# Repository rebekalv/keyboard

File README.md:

# 🚀 Build Your Dream Mechanical LED Keyboard with AVR DU! 🌟

Ever wanted to craft your own custom mechanical keyboard? Here's how I brought mine to life, step-by-step! 🛠️✨

---

### 🔧 **Project Highlights:**

- **Microcontroller Magic 🧠:**  
  Powered by the AVR64DU32 on a Curiosity Nano (cnano), this keyboard communicates seamlessly via USB-C using the Human Interface Device (HID) class. No soldering, no hassle—just plug and play!

- **Custom PCB in KiCad 💻:**  
  I designed a PCB to eliminate complex wiring, ensuring a sleek, professional layout. KiCad made it easy to customize my PCB, but managing library includes can be somewhat cumbersome.

- **Light Up the Keys! 🌈:**  
  Each key features a NeoPixel-compatible LED beneath, adding customizable lighting effects. LEDs are programmed directly alongside the keyboard firmware using MPLAB X IDE. Imagine the rainbow possibilities! 🌟 Due to a pcb schematic error (red circles), the ground and led data pin were swapped. Which is why lighting the leds will have to wait untill the arrival of a new pcb.

- **Custom 3D-Printed Case 🎨:**  
  The case is here! Designed with simplicity and style, it’s split into five parts for easy 3D printing 🖨️. All .stl files are in the 3D_keyboard_case folder, ready to print and assemble.

---

🎹 **DIY Tip:** If you're diving into mechanical keyboard projects, understanding matrix scanning and pcb tools like KiCad will open up endless customization!

Ready to create your own masterpiece? Let's type into the future! 🚀

## Component List
- Microcontroller: [AVR64DU32 curiosity nano](https://www.microchip.com/en-us/development-tool/ev59f82a)
- LEDs: [3.2x2.8mm sk6812 mini-E, reverse mount neopixel LEDs](https://www.aliexpress.com/item/1005005193716172.html)
- Diodes: [1N4148 DO-35 through hole diodes](https://www.aliexpress.com/item/1005006127068810.html)
- Switches: [JWICK V2 T1 Black Blue Tactile Switch 5pin RGB, Cherry MX](https://www.aliexpress.com/item/1005004226805283.html)
- Stabilizers for big switches: [PCB mounted Cherry MX stabilizers](https://es.aliexpress.com/item/1005004229140548.html)
- See-through Keycaps: [Polychroma V2 RGB Keycaps, Nordic ISO](https://www.maxgaming.no/no/keycaps/polychroma-v2-rgb-keycaps-131-pbt-polykarbonat-caps-nordic-iso)

## Milestones
1. 🖥️ [**Layout Creation:**](#layout-creation) Sketch the perfect keyboard design.
2. 🛠️ [**AVR Pin Setup:**](#avr-pin-setup) Map out pin connections and wiring.
3. 🔌 [**Component Selection:**](#component-selection) Choose the ideal switches, diodes, and LEDs.
4. 📐 [**PCB Design:**](#pcb-design) Craft your circuit board in KiCad and send it for manufacturing.
5. 🔧 [**Assembly:**](#assembly) Solder components onto the PCB.
6. 💻 [**Firmware Development:**](#firmware-development) Program the AVR for matrix scanning.
7. 🌈 **LED Integration:** Synchronize lighting with the firmware. (Suspended untill new pcb)
8. 🏗️ [**Case Design:**](#case-design) Plan and 3D print your custom keyboard case
9. 📚 **Document Everything:** Share your journey and insights.

### Layout Creation
I used https://www.keyboard-layout-editor.com/ to create an initial layout for my keyboard. If you want to regenerate this design, go to the website and insert the raw json data from `keyboard_layout/raw_data.json`. 

When your design is ready, you will need the outline of the keyboard for the pcb design. Go to https://plate.keeb.io/ and paste the raw json data. Then you can then download the outline as an svg file.

### AVR Pin Setup
The important thing in this step is to map out how many pins your keyboard needs, and if your microcontroller can provide that. My keyboard needs 5 rows and 15 columns, hence 20 pins. Looking at pinout on the [cnano website](https://www.microchip.com/en-us/development-tool/ev59f82a), it has 24 port pins. Excluding the usb detect, LED control and debugger LED pin, we are left with 21 available pins, which is enough for our keyboard.

Reading the datasheet for the avrdu, it reveals that the usart0 signal can be routed to 4 possible transmission pins. We will use this signal to control the leds, and I chose alternative 3, PD4, as the LED_DATA pin.

### Component Selection
Check the [component list](#component-list) for handy links! Going with popular, widely-used components simplifies the PCB design, because pre-existing footprints save time and effort. That's why I selected the reliable Cherry MX switches alongside the 1N4148 DO-35 diodes. Some Cherry MX switches feature an opening for LEDs to shine through, perfect for illuminating your keyboard (see the marking on the picture below). I opted to solder everything manually, so I chose through-hole diodes and ensured the LEDs were hand-solderable.

Pro tip: Also, go for PCB-mounted stabilizers—they're far easier to install than plate mounted, and the PCB outline already accommodates them.

### PCB Design
Now the real fun begins! 🚀 Or maybe the challenge? 🛠️

#### Schematic
In KiCad, you’ll start by creating a clear and accurate schematic. This is the blueprint for your circuit, mapping out connections between components and ensuring everything fits together logically. Double-check those connections and that the schema matches the data sheets—it’s much easier to catch errors here than on a finished PCB!

In my schematics, I connected all my switches and diodes and assigned them rows and columns as described in the keyboard outline. Further, I designed a symbol for the avrdu cnano, with the pinout corresponding to the datasheet. I connected the rows and columns to available port pins, and the grounds, voltages and led pin to their corresponding pins.

#### PCB and 3D model
After completing the schematic, the next step is designing the PCB layout. In the pcb editor you can import the outline from `keyboard_layout/keyboard-outline.svg`, which lets you know where to place your components. 

Then you import all the components from the schematic and arrange the them according to your design outline. All the symbols from the schematics will be translated into their corresponding footprint, which can be a bit confunsing and I recommend watching a youtube video explaing in detail.

Now you need to route all the traces, which might be the most time consuming. The netlist, which is thin lines between your components, will show how everything should be connected.

You can double check that your design matches your vision by using the 3D viewer in kicad and assigning .step files to all your footprints. Here is the 3d model of the front and the back of my pcb:

Now your design is ready for production! I used the fabrication tool kit in KiCad, to create a .zip file with gerber files. Then I went to https://jlcpcb.com/, uploaded the file and sent it to production. 

Pro tip: If there are no footprints available for your microcontroller, you can use footprints for similar microcontrollers and manually add or remove holes in the footprint editor to match you preffered controller.

### Assembly
This is a very straight forward process where you solder your components on the pcb. Start with the diodes and leds and do the switches last. Here is the assembled keyboard with stabilizers:

### Firmware Development
The `full_keyboard_avrdu.X` project structure:
 - **usb**: For checking and maintaining the usb-c connection
 - **hardware**: Functions for scanning columns and activating rows
 - **main**: Handles keypresses and sends HID codes over usb
 - **keyboard**: Mapping of keypresses to HID codes
 - **led**: In progress, here you find general LED functions which I used in my summer project

#### Matrix Scanning
When a button is pressed, its column and its row are connected together. Since the active row is low, it will pull the column down, from high to low. The code sequentially activates each row and scans through all columns to detect keypresses. It detects both the change from high to low (key down) and from low to high (key up). This process is repeated continuously to monitor key presses.

```
void IterateColumns(void) // called every 1 ms
{  
    // Iterate columns
        // Check key down event
        // Check key up event
    }
    
    // Go to the next row
 
    return;
}
```

On each key change, press or release, a hid code is sent with either a press down or a press up event. 

```
void KeyPressHandler(uint8_t currentRow)
{
    DetectKeyChanges(currentRow);
    
    if (keyChanges)
    {
        if (keyDown)
        {
            KeyDownEvent();
        }
        else
        {
            KeyUpEvent();
        }
    }
}
```

For special characters, modifiers can be used (shift and ctrl). In my code I check if a keypress corresponds to a modifier and then send the modifier down or up event. 

### LED Integration
I used the usart0 in the AVR in spi mode, to create a pulse-width modulated signal for neopixel LEDs. This will be used later to control the color scheme of the LEDs, but is for now on hold.

### Case Design
The keyboard now has a home! I designed an awesome 3D keyboard case that’s both practical and fun 🎉. It’s split into five pieces to fit my 3D printer 🖨️ and is super easy to assemble. All the 3D modules are available in the 3D_keyboard_case folder as .stl files, ready to print in any color you want! 🛠️ For the creative minds, I’ve included the original DesignSpark Mechanical file 🖌️, so you can tweak, customize, or modify it using their 3D modeling software. Whether you glue it together, enhance it further, or leave it as is, this case is ready to elevate your keyboard project! 🚀🌈

  - Keyboard case top

- Keyboard case bottom

- Keyboard case tilted support

### Conclusion
Now you know how to create a custom, matrix keyboard using an AVR64DU32 Curiosity Nano. By using the USB-C HID class, our keyboard communicates directly with the computer and wiring was simplified using a custom made PCB. LEDs were included under each key and what is missing is to create a fitting case for the keyboard.

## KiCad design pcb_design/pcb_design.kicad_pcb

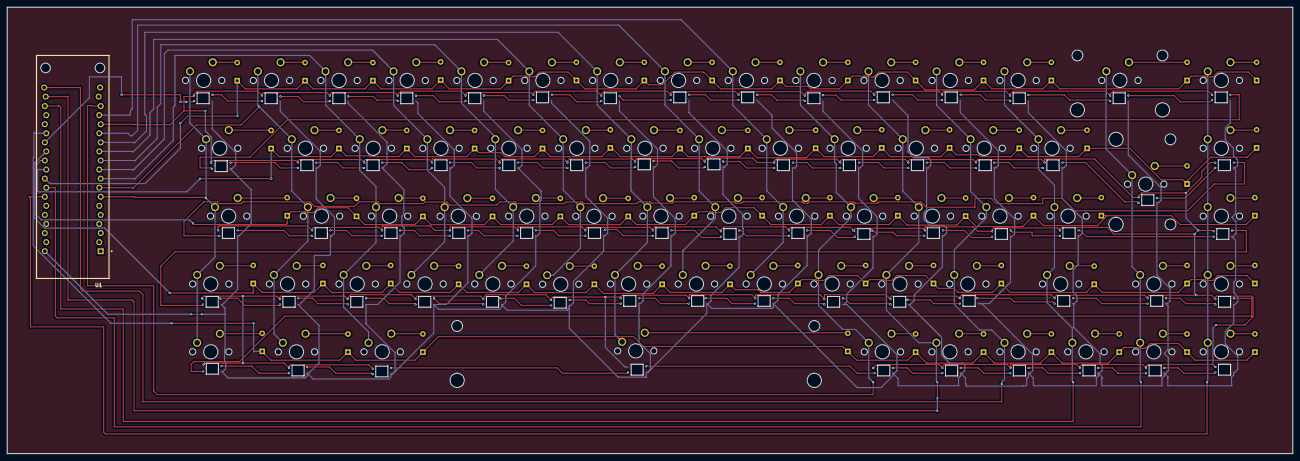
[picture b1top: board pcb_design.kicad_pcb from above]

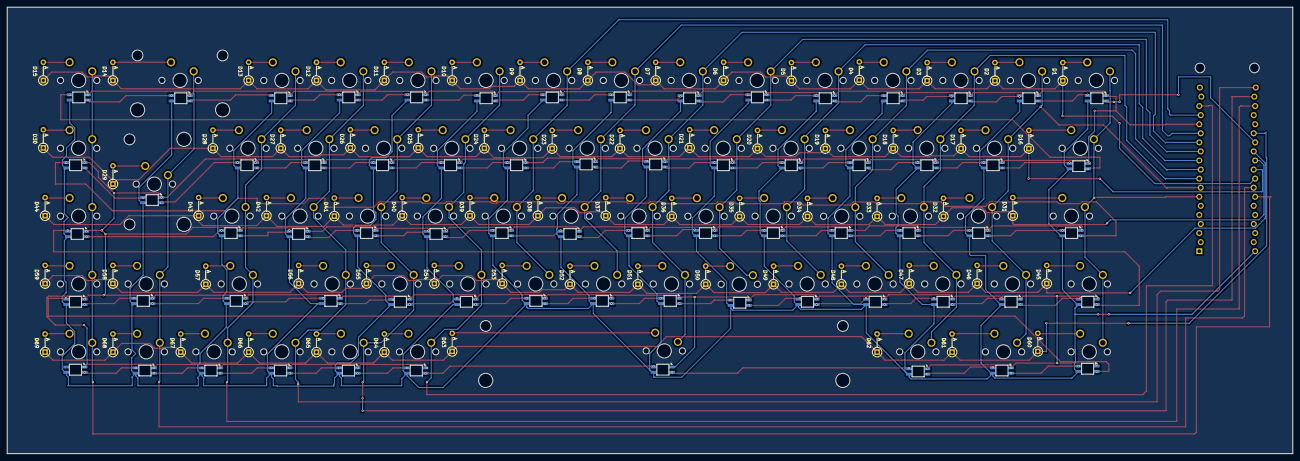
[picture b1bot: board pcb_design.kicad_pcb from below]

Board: 2 copper layers, 360.0 x 125.0 mm, 211 parts (138 on the bottom side), 160 nets.

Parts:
D1, D2, D3, D4, D5, D6, D7, D8, D9, D10, D11, D12, D13, D14, D15, D16, D17, D18, D19, D20, D21, D22, D23, D24, D25, D26, D27, D28, D29, D30, D31, D32, D33, D34, D35, D36, D37, D38, D39, D40, D41, D42, D43, D44, D45, D46, D47, D48, D49, D50, D51, D52, D53, D54, D55, D56, D57, D58, D59, D60, D61, D62, D63, D64, D65, D66, D67, D68, D69: D_Small; D_DO-35_SOD27_P5.08mm_Vertical_AnodeUp
LED1, LED2, LED3, LED4, LED5, LED6, LED7, LED8, LED9, LED10, LED11, LED12, LED13, LED14, LED15, LED16, LED17, LED18, LED19, LED20, LED21, LED22, LED23, LED24, LED25, LED26, LED27, LED28, LED29, LED30, LED31, LED32, LED33, LED34, LED35, LED36, LED37, LED38, LED39, LED40, LED41, LED42, LED43, LED44, LED45, LED46, LED47, LED48, LED49, LED50, LED51, LED52, LED53, LED54, LED55, LED56, LED57, LED58, LED59, LED60, LED61, LED62, LED63, LED64, LED65, LED66, LED67, LED68, LED69: SK6812MINI-E; SK6812-MINI-E
MX1, MX2, MX3, MX4, MX5, MX6, MX7, MX8, MX9, MX10, MX11, MX12, MX13, MX14, MX15, MX16, MX17, MX18, MX19, MX20, MX21, MX22, MX23, MX24, MX25, MX26, MX27, MX28, MX29, MX30, MX31, MX32, MX33, MX34, MX35, MX36, MX37, MX38, MX39, MX40, MX41, MX42, MX43, MX44, MX45, MX46, MX47, MX48, MX49, MX50, MX51, MX52, MX53, MX54, MX55, MX56, MX57, MX58, MX59, MX60, MX61, MX62, MX63, MX64, MX65, MX66, MX67, MX68, MX69: MX_SW_solder; SW_MX_1u
S1: MX_stab; STAB_MX_6.25u
S2, S3: MX_stab; STAB_MX_2u
U1: AVR_CNANO; cnano

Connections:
LED_pin: LED1.4 (DIN), U1.26 (PD4)
unnamed: D1.2 (A), MX1.2
unnamed: D2.2 (A), MX2.2
unnamed: D3.2 (A), MX3.2
unnamed: D4.2 (A), MX4.2
unnamed: D5.2 (A), MX5.2
unnamed: D6.2 (A), MX6.2
unnamed: D7.2 (A), MX7.2
unnamed: D8.2 (A), MX8.2
unnamed: D9.2 (A), MX9.2
unnamed: D10.2 (A), MX10.2
unnamed: D11.2 (A), MX11.2
unnamed: D12.2 (A), MX12.2
unnamed: D13.2 (A), MX13.2
unnamed: D14.2 (A), MX14.2
unnamed: D15.2 (A), MX15.2
unnamed: D16.2 (A), MX16.2
unnamed: D17.2 (A), MX17.2
unnamed: D18.2 (A), MX18.2
unnamed: D19.2 (A), MX19.2
unnamed: D20.2 (A), MX20.2
unnamed: D21.2 (A), MX21.2
unnamed: D22.2 (A), MX22.2
unnamed: D23.2 (A), MX23.2
unnamed: D24.2 (A), MX24.2
unnamed: D25.2 (A), MX25.2
unnamed: D26.2 (A), MX26.2
unnamed: D27.2 (A), MX27.2
unnamed: D28.2 (A), MX28.2
unnamed: D29.2 (A), MX29.2
unnamed: D30.2 (A), MX30.2
unnamed: D31.2 (A), MX31.2
unnamed: D32.2 (A), MX32.2
unnamed: D33.2 (A), MX33.2
unnamed: D34.2 (A), MX34.2
unnamed: D35.2 (A), MX35.2
unnamed: D36.2 (A), MX36.2
unnamed: D37.2 (A), MX37.2
unnamed: D38.2 (A), MX38.2
unnamed: D39.2 (A), MX39.2
unnamed: D40.2 (A), MX40.2
unnamed: D41.2 (A), MX41.2
unnamed: D42.2 (A), MX42.2
unnamed: D43.2 (A), MX43.2
unnamed: D44.2 (A), MX44.2
unnamed: D45.2 (A), MX45.2
unnamed: D46.2 (A), MX46.2
unnamed: D47.2 (A), MX47.2
unnamed: D48.2 (A), MX48.2
unnamed: D49.2 (A), MX49.2
unnamed: D50.2 (A), MX50.2
unnamed: D51.2 (A), MX51.2
unnamed: D52.2 (A), MX52.2
unnamed: D53.2 (A), MX53.2
unnamed: D54.2 (A), MX54.2
unnamed: D55.2 (A), MX55.2
unnamed: D56.2 (A), MX56.2
unnamed: D57.2 (A), MX57.2
unnamed: D58.2 (A), MX58.2
unnamed: D59.2 (A), MX59.2
unnamed: D60.2 (A), MX60.2
unnamed: D61.2 (A), MX61.2
unnamed: D62.2 (A), MX62.2
unnamed: D63.2 (A), MX63.2
unnamed: D64.2 (A), MX64.2
unnamed: D65.2 (A), MX65.2
unnamed: D66.2 (A), MX66.2
unnamed: D67.2 (A), MX67.2
unnamed: D68.2 (A), MX68.2
unnamed: D69.2 (A), MX69.2
unnamed: LED1.2 (DOUT), LED2.4 (DIN)
unnamed: LED2.2 (DOUT), LED3.4 (DIN)
unnamed: LED3.2 (DOUT), LED4.4 (DIN)
unnamed: LED4.2 (DOUT), LED5.4 (DIN)
unnamed: LED5.2 (DOUT), LED6.4 (DIN)
unnamed: LED6.2 (DOUT), LED7.4 (DIN)
unnamed: LED7.2 (DOUT), LED8.4 (DIN)
unnamed: LED8.2 (DOUT), LED9.4 (DIN)
unnamed: LED10.2 (DOUT), LED11.4 (DIN)
unnamed: LED9.2 (DOUT), LED10.4 (DIN)
unnamed: LED11.2 (DOUT), LED12.4 (DIN)
unnamed: LED12.2 (DOUT), LED13.4 (DIN)
unnamed: LED13.2 (DOUT), LED14.4 (DIN)
unnamed: LED14.2 (DOUT), LED15.4 (DIN)
unnamed: LED15.2 (DOUT), LED16.4 (DIN)
unnamed: LED16.2 (DOUT), LED17.4 (DIN)
unnamed: LED17.2 (DOUT), LED18.4 (DIN)
unnamed: LED18.2 (DOUT), LED19.4 (DIN)
unnamed: LED19.2 (DOUT), LED20.4 (DIN)
unnamed: LED20.2 (DOUT), LED21.4 (DIN)
unnamed: LED21.2 (DOUT), LED22.4 (DIN)
unnamed: LED22.2 (DOUT), LED23.4 (DIN)
unnamed: LED23.2 (DOUT), LED24.4 (DIN)
unnamed: LED24.2 (DOUT), LED25.4 (DIN)
unnamed: LED25.2 (DOUT), LED26.4 (DIN)
unnamed: LED26.2 (DOUT), LED27.4 (DIN)
unnamed: LED27.2 (DOUT), LED28.4 (DIN)
unnamed: LED28.2 (DOUT), LED29.4 (DIN)
unnamed: LED29.2 (DOUT), LED30.4 (DIN)
unnamed: LED30.2 (DOUT), LED31.4 (DIN)
unnamed: LED31.2 (DOUT), LED32.4 (DIN)
unnamed: LED32.2 (DOUT), LED33.4 (DIN)
unnamed: LED33.2 (DOUT), LED34.4 (DIN)
unnamed: LED34.2 (DOUT), LED35.4 (DIN)
unnamed: LED35.2 (DOUT), LED36.4 (DIN)
unnamed: LED36.2 (DOUT), LED37.4 (DIN)
unnamed: LED37.2 (DOUT), LED38.4 (DIN)
unnamed: LED38.2 (DOUT), LED39.4 (DIN)
unnamed: LED39.2 (DOUT), LED40.4 (DIN)
unnamed: LED40.2 (DOUT), LED41.4 (DIN)
unnamed: LED41.2 (DOUT), LED42.4 (DIN)
unnamed: LED42.2 (DOUT), LED43.4 (DIN)
unnamed: LED43.2 (DOUT), LED44.4 (DIN)
unnamed: LED44.2 (DOUT), LED45.4 (DIN)
unnamed: LED45.2 (DOUT), LED46.4 (DIN)
unnamed: LED46.2 (DOUT), LED47.4 (DIN)
unnamed: LED47.2 (DOUT), LED48.4 (DIN)
unnamed: LED48.2 (DOUT), LED49.4 (DIN)
unnamed: LED49.2 (DOUT), LED50.4 (DIN)
unnamed: LED50.2 (DOUT), LED51.4 (DIN)
unnamed: LED51.2 (DOUT), LED52.4 (DIN)
unnamed: LED52.2 (DOUT), LED53.4 (DIN)
unnamed: LED53.2 (DOUT), LED54.4 (DIN)
unnamed: LED54.2 (DOUT), LED55.4 (DIN)
unnamed: LED55.2 (DOUT), LED56.4 (DIN)
unnamed: LED56.2 (DOUT), LED57.4 (DIN)
unnamed: LED57.2 (DOUT), LED58.4 (DIN)
unnamed: LED58.2 (DOUT), LED59.4 (DIN)
unnamed: LED59.2 (DOUT), LED60.4 (DIN)
unnamed: LED60.2 (DOUT), LED61.4 (DIN)
unnamed: LED61.2 (DOUT), LED62.4 (DIN)
unnamed: LED62.2 (DOUT), LED63.4 (DIN)
unnamed: LED63.2 (DOUT), LED64.4 (DIN)
unnamed: LED64.2 (DOUT), LED65.4 (DIN)
unnamed: LED65.2 (DOUT), LED66.4 (DIN)
unnamed: LED66.2 (DOUT), LED67.4 (DIN)
unnamed: LED67.2 (DOUT), LED68.4 (DIN)
unnamed: LED68.2 (DOUT), LED69.4 (DIN)
VDD: LED1.1 (VDD), LED2.1 (VDD), LED3.1 (VDD), LED4.1 (VDD), LED5.1 (VDD), LED6.1 (VDD), LED7.1 (VDD), LED8.1 (VDD), LED9.1 (VDD), LED10.1 (VDD), LED11.1 (VDD), LED12.1 (VDD), LED13.1 (VDD), LED14.1 (VDD), LED15.1 (VDD), LED16.1 (VDD), LED17.1 (VDD), LED18.1 (VDD), LED19.1 (VDD), LED20.1 (VDD), LED21.1 (VDD), LED22.1 (VDD), LED23.1 (VDD), LED24.1 (VDD), LED25.1 (VDD), LED26.1 (VDD), LED27.1 (VDD), LED28.1 (VDD), LED29.1 (VDD), LED30.1 (VDD), LED31.1 (VDD), LED32.1 (VDD), LED33.1 (VDD), LED34.1 (VDD), LED35.1 (VDD), LED36.1 (VDD), LED37.1 (VDD), LED38.1 (VDD), LED39.1 (VDD), LED40.1 (VDD), LED41.1 (VDD), LED42.1 (VDD), LED43.1 (VDD), LED44.1 (VDD), LED45.1 (VDD), LED46.1 (VDD), LED47.1 (VDD), LED48.1 (VDD), LED49.1 (VDD), LED50.1 (VDD), LED51.1 (VDD), LED52.1 (VDD), LED53.1 (VDD), LED54.1 (VDD), LED55.1 (VDD), LED56.1 (VDD), LED57.1 (VDD), LED58.1 (VDD), LED59.1 (VDD), LED60.1 (VDD), LED61.1 (VDD), LED62.1 (VDD), LED63.1 (VDD), LED64.1 (VDD), LED65.1 (VDD), LED66.1 (VDD), LED67.1 (VDD), LED68.1 (VDD), LED69.1 (VDD), U1.38 (VBUS)
VSS: LED1.3 (VSS), LED2.3 (VSS), LED3.3 (VSS), LED4.3 (VSS), LED5.3 (VSS), LED6.3 (VSS), LED7.3 (VSS), LED8.3 (VSS), LED9.3 (VSS), LED10.3 (VSS), LED11.3 (VSS), LED12.3 (VSS), LED13.3 (VSS), LED14.3 (VSS), LED15.3 (VSS), LED16.3 (VSS), LED17.3 (VSS), LED18.3 (VSS), LED19.3 (VSS), LED20.3 (VSS), LED21.3 (VSS), LED22.3 (VSS), LED23.3 (VSS), LED24.3 (VSS), LED25.3 (VSS), LED26.3 (VSS), LED27.3 (VSS), LED28.3 (VSS), LED29.3 (VSS), LED30.3 (VSS), LED31.3 (VSS), LED32.3 (VSS), LED33.3 (VSS), LED34.3 (VSS), LED35.3 (VSS), LED36.3 (VSS), LED37.3 (VSS), LED38.3 (VSS), LED39.3 (VSS), LED40.3 (VSS), LED41.3 (VSS), LED42.3 (VSS), LED43.3 (VSS), LED44.3 (VSS), LED45.3 (VSS), LED46.3 (VSS), LED47.3 (VSS), LED48.3 (VSS), LED49.3 (VSS), LED50.3 (VSS), LED51.3 (VSS), LED52.3 (VSS), LED53.3 (VSS), LED54.3 (VSS), LED55.3 (VSS), LED56.3 (VSS), LED57.3 (VSS), LED58.3 (VSS), LED59.3 (VSS), LED60.3 (VSS), LED61.3 (VSS), LED62.3 (VSS), LED63.3 (VSS), LED64.3 (VSS), LED65.3 (VSS), LED66.3 (VSS), LED67.3 (VSS), LED68.3 (VSS), LED69.3 (VSS), U1.15 (GND)
col0: MX1.1, MX16.1, MX31.1, MX45.1, MX60.1, U1.7 (PA0)
col1: MX2.1, MX17.1, MX32.1, MX46.1, MX61.1, U1.8 (PA1)
col2: MX3.1, MX18.1, MX33.1, MX47.1, MX62.1, U1.9 (PA2)
col3: MX4.1, MX19.1, MX34.1, MX48.1, U1.10 (PA3)
col4: MX5.1, MX20.1, MX35.1, MX49.1, U1.11 (PA4)
col5: MX6.1, MX21.1, MX36.1, MX50.1, U1.12 (PA5)
col6: MX7.1, MX22.1, MX37.1, MX51.1, MX63.1, U1.13 (PA6)
col7: MX8.1, MX23.1, MX38.1, MX52.1, U1.14 (PA7)
col8: MX9.1, MX24.1, MX39.1, MX53.1, U1.16 (PD6)
col9: MX10.1, MX25.1, MX40.1, MX54.1, MX64.1, U1.17 (PD7)
col10: MX11.1, MX26.1, MX41.1, MX55.1, MX65.1, U1.21 (PF0)
col11: MX12.1, MX27.1, MX42.1, MX56.1, MX66.1, U1.20 (PF1)
col12: MX13.1, MX28.1, MX43.1, MX57.1, MX67.1, U1.22 (PF3)
col13: MX14.1, MX29.1, MX58.1, MX68.1, U1.31 (PF5)
col14: MX15.1, MX30.1, MX44.1, MX59.1, MX69.1, U1.32 (PF4)
row0: D1.1 (K), D2.1 (K), D3.1 (K), D4.1 (K), D5.1 (K), D6.1 (K), D7.1 (K), D8.1 (K), D9.1 (K), D10.1 (K), D11.1 (K), D12.1 (K), D13.1 (K), D14.1 (K), D15.1 (K), U1.30 (PD0)
row1: D16.1 (K), D17.1 (K), D18.1 (K), D19.1 (K), D20.1 (K), D21.1 (K), D22.1 (K), D23.1 (K), D24.1 (K), D25.1 (K), D26.1 (K), D27.1 (K), D28.1 (K), D29.1 (K), D30.1 (K), U1.29 (PD1)
row2: D31.1 (K), D32.1 (K), D33.1 (K), D34.1 (K), D35.1 (K), D36.1 (K), D37.1 (K), D38.1 (K), D39.1 (K), D40.1 (K), D41.1 (K), D42.1 (K), D43.1 (K), D44.1 (K), U1.28 (PD2)
row3: D45.1 (K), D46.1 (K), D47.1 (K), D48.1 (K), D49.1 (K), D50.1 (K), D51.1 (K), D52.1 (K), D53.1 (K), D54.1 (K), D55.1 (K), D56.1 (K), D57.1 (K), D58.1 (K), D59.1 (K), U1.27 (PD3)
row4: D60.1 (K), D61.1 (K), D62.1 (K), D63.1 (K), D64.1 (K), D65.1 (K), D66.1 (K), D67.1 (K), D68.1 (K), D69.1 (K), U1.25 (PD5)

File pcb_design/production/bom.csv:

Designator,Footprint,Quantity,Value,LCSC Part #
"D1, D10, D11, D12, D13, D14, D15, D16, D17, D18, D19, D2, D20, D21, D22, D23, D24, D25, D26, D27, D28, D29, D3, D30, D31, D32, D33, D34, D35, D36, D37, D38, D39, D4, D40, D41, D42, D43, D44, D45, D46, D47, D48, D49, D5, D50, D51, D52, D53, D54, D55, D56, D57, D58, D59, D6, D60, D61, D62, D63, D64, D65, D66, D67, D68, D69, D7, D8, D9",D_DO-35_SOD27_P5.08mm_Vertical_AnodeUp,69,D_Small,
"LED1, LED10, LED11, LED12, LED13, LED14, LED15, LED16, LED17, LED18, LED19, LED2, LED20, LED21, LED22, LED23, LED24, LED25, LED26, LED27, LED28, LED29, LED3, LED30, LED31, LED32, LED33, LED34, LED35, LED36, LED37, LED38, LED39, LED4, LED40, LED41, LED42, LED43, LED44, LED45, LED46, LED47, LED48, LED49, LED5, LED50, LED51, LED52, LED53, LED54, LED55, LED56, LED57, LED58, LED59, LED6, LED60, LED61, LED62, LED63, LED64, LED65, LED66, LED67, LED68, LED69, LED7, LED8, LED9",SK6812-MINI-E,69,SK6812MINI-E,
"MX1, MX10, MX11, MX12, MX13, MX14, MX15, MX16, MX17, MX18, MX19, MX2, MX20, MX21, MX22, MX23, MX24, MX25, MX26, MX27, MX28, MX29, MX3, MX30, MX31, MX32, MX33, MX34, MX35, MX36, MX37, MX38, MX39, MX4, MX40, MX41, MX42, MX43, MX44, MX45, MX46, MX47, MX48, MX49, MX5, MX50, MX51, MX52, MX53, MX54, MX55, MX56, MX57, MX58, MX59, MX6, MX60, MX61, MX62, MX63, MX64, MX65, MX66, MX67, MX68, MX69, MX7, MX8, MX9",SW_MX_1u,69,MX_SW_solder,
S1,STAB_MX_6.25u,1,MX_stab,
"S2, S3",STAB_MX_2u,2,MX_stab,
U1,cnano,1,AVR_CNANO,

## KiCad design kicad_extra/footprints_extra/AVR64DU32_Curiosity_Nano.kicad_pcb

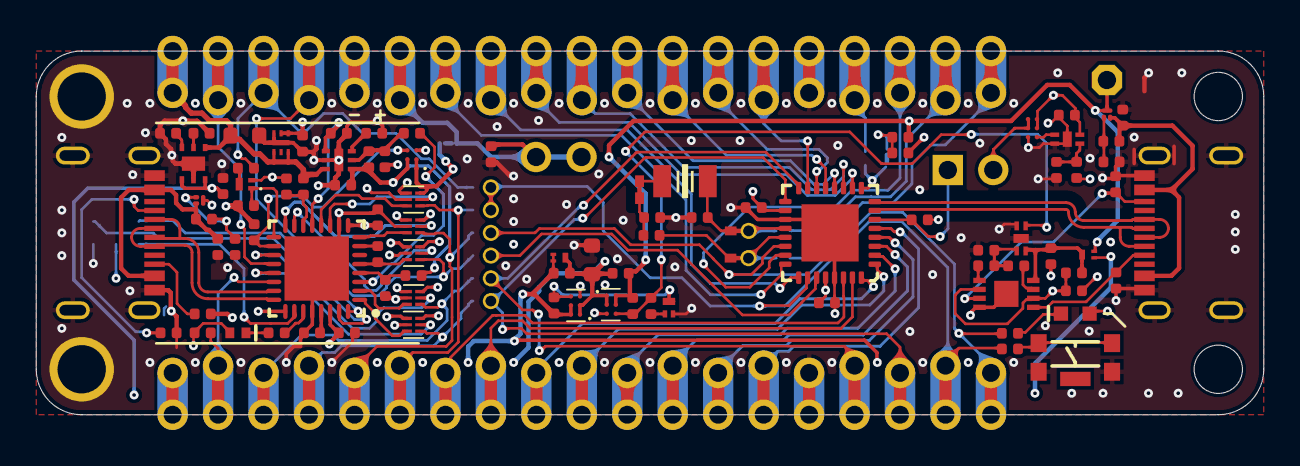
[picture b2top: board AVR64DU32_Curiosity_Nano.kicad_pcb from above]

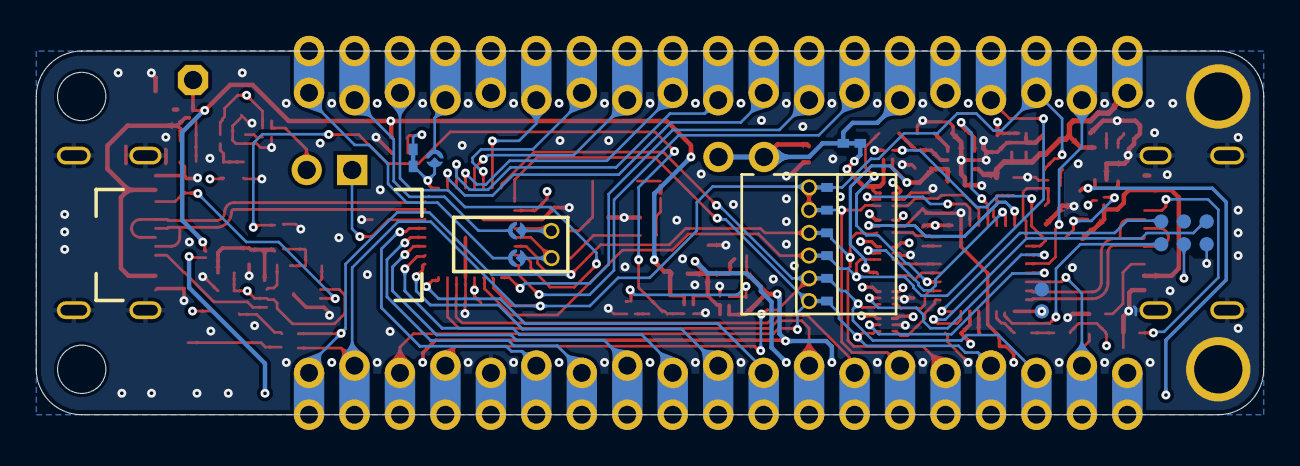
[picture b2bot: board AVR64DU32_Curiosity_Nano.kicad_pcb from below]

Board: 4 copper layers, 68.6 x 20.3 mm, 114 parts (17 on the bottom side), 106 nets.

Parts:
C100, C101, C102, C103, C104, C105, C106, C107, C200, C201, C202, C203, C204, C206, C207, C208, C209, C301, C303: CAP_C_0402
C205, C300: CAP_C_0603
D100: LED_0603_Yellow
D200: LED_0402_GREEN
D300, D301: X3-DSN1006-3
J100: CON_EDGE_CNANO-38
J101, J102, J103, J104, J105, J106, J109, J110: CON_JMPR_0402_PCB_TRACE_LINK_0.9mm_PAD_0.6mm_PTH
J107, J108, J113: CON_JMPR_1mmX1mm_ROUND_SOLDER-STRAP
J111, J116, J200: CON_JMPR_0402_PCB_TRACE_LINK
J112, J203: CON_USB2.0-C_RCPT_SMD_RA_KLS_KLS1-5409
J114: HDR_M_2.54_1x2_U_TH-PIP_V_WCON_1125-1102S0S113R1
J115: HDR_M_2.54_1x1
J201: CON_JMPR_2.54_1x2_TH_PCB_TRACE_LINK
J202: TESTPOINT_ARRAY_2x3_1.27mm_pitch_SMD
JP100: Jumper_Mechanical
LABEL1: 08-10015
Q100, Q201: LGA-3_GSD_0.7x0.6_CSD25501F3
Q200, Q300: X1-DFN1006-3
R100, R101, R102, R103, R104, R105, R106, R107, R108, R109, R110, R200, R201, R202, R203, R204, R205, R206, R207, R208, R209, R210, R211, R212, R213, R214, R215, R216, R217, R218, R300, R301, R302, R303, R304, R305, R306, R307, R308: RES_C_0402
SW100: SW_TACT_SMD_KLS_L-KLS7-TS0304A-2-300-T
TP200, TP201: TP_3.6X2.7
TP202, TP203: CON_TP_0.8dia_SMD_with_Test_Jig_Layer
U100: VQFN-32_5X5_EP3.2X3.2
U101: WLCSP-6_L1W1.5H0.5
U102, U303: TDFN-4_1.6x1.2
U200: MLF-6 1.6X1.6mm
U201, U300, U301: MIC94163_1.5MM_1MM
U202: VDFN-6_2x2_EP0.8X1.40
U203: DFN-6_1.2x1.2
U204, U205, U207, U208, U209: X2-DFN1010-6
U206: QFN-32_5X5_EP3.6x3.6_L
U302: TDFN-8_2X3_EP1.46X1.36
Y100: CRYSTAL_VMK3_L3.2W1.5H0.9

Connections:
BOOT: TP202.1, U206.25
CDC_RX: J100.3, J101.1, U208.4
CDC_RX_CTRL: U206.19, U208.5
CDC_TX: J100.4, J103.1, U209.4
CDC_TX_CTRL: U206.21, U209.5
DAC: R208.2, U206.3
DBG0: J100.35, J104.1, U207.4
DBG0_CTRL: U206.15, U207.5
DBG1: J100.5, J105.1, U205.4
DBG1_CTRL: U205.5, U206.16
DBG2: J100.6, J106.1, U204.4
DBG2_CTRL: U204.5, U206.11
DBG2_GPIO: U204.3, U206.12
DBG3: J100.36, J102.1, R209.2
DBG3_CTRL: Q200.1, R210.1, U206.17
GND: C100.2, C101.2, C103.1, C104.1, C105.2, C106.1, C107.2, C200.1, C201.2, C202.1, C203.1, C204.1, C205.1, C206.1, C207.2, C209.1, C300.1, C301.1, C303.1, J100.15, J100.24, J100.34, J112.1, J112.2, J112.3, J112.4, J112.A1/B12, J112.B1/A12, J202.2, J203.1, J203.2, J203.3, J203.4, J203.A1/B12, J203.B1/A12, Q200.2, Q300.2, R100.1, R101.2, R102.2, R105.2, R107.1, R109.1, R203.2, R204.2, R205.1, R206.1, R207.1, R210.2, R211.2, R213.2, R214.2, R216.2, R217.2, R306.1, SW100.1, SW100.2, TP200.1, TP201.1, TP203.1, U100.19, U100.29, U100.33, U101.C1, U102.2, U102.5, U200.2, U200.7, U201.C1, U202.5, U202.7, U203.3, U203.7, U204.2, U205.2, U206.10, U206.28, U206.33, U207.2, U208.2, U209.2, U300.C1, U301.C1, U302.4, U302.9, U303.2, U303.5
ID_SYS: J100.2, R218.1, U206.22
MUX_CONTROL: R302.2, R307.1, U300.C2, U303.1
NetC102_1: C102.1, Q100.1, R101.1
NetC104_2: C104.2, J109.1, Y100.1
NetC105_1: C105.1, J111.1, R110.1
NetC201_1: C201.1, U200.6
NetC206_2: C206.2, U202.2
NetC208_1: C208.1, Q201.1, R214.1
NetD100_2: D100.2, R104.2
NetD200_2: D200.2, R215.1
NetJ110_1: J110.1, R110.2
NetJ111_2: J111.2, Y100.2
NetJ114_2: J114.2, U101.A1, U101.B1
NetJ116_1: J116.1, R108.1, R109.2
NetJ203_A5: J203.A5, R217.1
NetJ203_B5: J203.B5, R216.1
NetQ200_3: Q200.3, R209.1
NetQ300_1: Q300.1, R307.2
NetQ300_3: Q300.3, R303.1, U301.C2
NetR103_2: R103.2, SW100.3, SW100.4
NetR106_1: R106.1, R107.2, U102.3
NetR211_1: R211.1, U202.3
NetR305_2: R305.2, U302.1
NetR308_1: R308.1, U302.7
NetU101_C2: U101.C2, U102.1
PA0_USART0_TX: J100.7, U100.30
PA1_USART0_RX: J100.8, U100.31
PA2_I2C0_SDA: J100.9, U100.32
PA3_I2C0_SCL: J100.10, U100.1
PA4_SPI0_MOSI: J100.11, U100.2
PA5_SPI0_MISO: J100.12, U100.3
PA6_SPI0_SCK: J100.13, U100.4
PA7_SPI0_SS: J100.14, U100.5
PC3: J100.23, J113.2
PC3_VBUS_TARGET_DETECT: J113.1, J116.2, U100.9
PD0_AIN0: J100.30, U100.10
PD1_AIN1: J100.29, U100.11
PD2_AIN2: J100.28, U100.12
PD3_AIN3: J100.27, U100.13
PD4_AIN4: J100.26, U100.14
PD5_AIN5: J100.25, U100.15
PD6_USART1_TX: J100.16, J101.2, U100.16
PD7_USART1_RX: J100.17, J103.2, U100.17
PF0: J100.21, J107.2
PF0_XTAL32K1: J107.1, J109.2, U100.20
PF1: J100.20, J108.2
PF1_XTAL32K2: J108.1, J110.2, U100.21
PF2_LED0_DBG1: J100.19, J105.2, R104.1, U100.22
PF3: J100.22, U100.23
PF4_AIN20: J100.32, U100.24
PF5_AIN21: J100.31, U100.25
PF6_SW0_DBG2: J100.18, J102.2, J106.2, R103.1, U100.26
PF7_UPDI: J104.2, U100.27
REG_ADJUST: R201.2, R206.2, R208.1, U200.5
REG_ENABLE: R204.1, U200.1, U206.13
S0_0_RX: R212.1, U206.5, U207.3
S0_2_TX: R212.2, U206.7
S0_3_CLK: U205.3, U206.8
S1_0_TX: U206.1, U209.3
S1_1_RX: U206.2, U208.3
STATUS_LED: R215.2, U206.27
SWCLK: J202.1, U206.31
SWDIO: J202.5, U206.32
TARGET_CC1: J112.A5, R105.1, U302.5
TARGET_CC2: J112.B5, R102.1, U302.3
USBD_N: J203.A7, J203.B7, U206.23
USBD_P: J203.A6, J203.B6, U206.24
USBT_N: J112.A7, J112.B7, U100.7
USBT_P: J112.A6, J112.B6, U100.8
VBUS_ADC: R200.2, R205.2, U206.14
VBUS_DEBUG: C208.2, J203.A4/B9, J203.B4/A9, Q201.2, R213.1
VBUS_DEBUG_DELAYED: D300.2, D300.3, D301.2, Q201.3, R301.1, R303.2, U301.A2, U301.B2
VBUS_MUX_OUT: C204.2, C300.2, D300.1, R300.1, R301.2, U202.4, U202.6, U300.A1, U300.B1, U301.A1, U301.B1
VBUS_MUX_VCC: C301.2, D301.1, R304.2, U302.8, U303.4
VBUS_TARGET: C102.2, J112.A4/B9, J112.B4/A9, Q100.2, R100.2
VBUS_TARGET_DELAYED: D301.3, J115.1, Q100.3, R108.2, R300.2, R302.1, U300.A2, U300.B2
VBUS_TARGET_EN: C303.2, R305.1, R308.2, U303.3
VCC_EDGE: C103.2, J100.33, J200.2, J201.1
VCC_LEVEL: J200.1, U201.A1, U201.B1, U204.6, U205.6, U207.6, U208.6, U209.6
VCC_MCU_CORE: C209.2, U206.29
VCC_P3V3: C107.1, C202.2, C203.2, C207.1, D200.1, J202.4, R218.2, U101.A2, U101.B2, U102.4, U203.1, U203.2, U204.1, U205.1, U206.9, U206.30, U207.1, U208.1, U209.1
VCC_REGULATOR: C200.2, R201.1, R202.2, U200.4, U201.A2, U201.B2
VCC_TARGET: C100.1, C101.1, D100.1, J201.2, R106.2, U100.18, U100.28
VCC_VBUS: C205.2, J100.38, R200.1, U200.3, U202.1, U203.4, U203.6
VREF_P0V320: R304.1, R306.2, U302.2, U302.6
VTG_ADC: R202.1, R207.2, U206.4
VTG_EN: R203.1, U201.C2, U206.18
VUSB_TARGET: C106.2, J114.1, U100.6
~SRST: J202.6, U206.26
~VOFF: J100.37, U206.20

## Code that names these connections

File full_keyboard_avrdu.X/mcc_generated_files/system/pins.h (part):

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#define ROW3_EnableInterruptForLowLevelSensing() do { PORTD.PIN3CTRL = (PORTD.PIN3CTRL & ~PORT_ISC_gm) | 0x5 ; } while(0)
#define PD3_SetInterruptHandler ROW3_SetInterruptHandler

//get/set LED_PIN aliases
#define LED_PIN_SetHigh() do { PORTD_OUTSET = 0x10; } while(0)
#define LED_PIN_SetLow() do { PORTD_OUTCLR = 0x10; } while(0)
#define LED_PIN_Toggle() do { PORTD_OUTTGL = 0x10; } while(0)
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
/**
 * @ingroup  pinsdriver
 * @brief Default Interrupt Handler for COL0 pin. 
 *        This is a predefined interrupt handler to be used together with the COL0_SetInterruptHandler() method.
 *        This handler is called every time the COL0 ISR is executed. 
 * @pre PIN_MANAGER_Initialize() has been called at least once
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
/**
 * @ingroup  pinsdriver
 * @brief Interrupt Handler Setter for COL0 pin input-sense-config functionality.
 *        Allows selecting an interrupt handler for COL0 at application runtime
 * @pre PIN_MANAGER_Initialize() has been called at least once
 * @param InterruptHandler function pointer.
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
/**
 * @ingroup  pinsdriver
 * @brief Default Interrupt Handler for COL1 pin. 
 *        This is a predefined interrupt handler to be used together with the COL1_SetInterruptHandler() method.
 *        This handler is called every time the COL1 ISR is executed. 
 * @pre PIN_MANAGER_Initialize() has been called at least once
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
/**
 * @ingroup  pinsdriver
 * @brief Interrupt Handler Setter for COL1 pin input-sense-config functionality.
 *        Allows selecting an interrupt handler for COL1 at application runtime
 * @pre PIN_MANAGER_Initialize() has been called at least once
 * @param InterruptHandler function pointer.
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
/**
 * @ingroup  pinsdriver
 * @brief Default Interrupt Handler for COL2 pin. 
 *        This is a predefined interrupt handler to be used together with the COL2_SetInterruptHandler() method.
 *        This handler is called every time the COL2 ISR is executed. 
 * @pre PIN_MANAGER_Initialize() has been called at least once
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
/**
 * @ingroup  pinsdriver
 * @brief Interrupt Handler Setter for COL2 pin input-sense-config functionality.
 *        Allows selecting an interrupt handler for COL2 at application runtime
 * @pre PIN_MANAGER_Initialize() has been called at least once
 * @param InterruptHandler function pointer.
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
/**
 * @ingroup  pinsdriver
 * @brief Default Interrupt Handler for COL3 pin. 
 *        This is a predefined interrupt handler to be used together with the COL3_SetInterruptHandler() method.
 *        This handler is called every time the COL3 ISR is executed. 
 * @pre PIN_MANAGER_Initialize() has been called at least once
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
/**
 * @ingroup  pinsdriver
 * @brief Interrupt Handler Setter for COL3 pin input-sense-config functionality.
 *        Allows selecting an interrupt handler for COL3 at application runtime
 * @pre PIN_MANAGER_Initialize() has been called at least once
 * @param InterruptHandler function pointer.
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
/**
 * @ingroup  pinsdriver
 * @brief Default Interrupt Handler for COL4 pin. 
 *        This is a predefined interrupt handler to be used together with the COL4_SetInterruptHandler() method.
 *        This handler is called every time the COL4 ISR is executed. 
 * @pre PIN_MANAGER_Initialize() has been called at least once
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
/**
 * @ingroup  pinsdriver
 * @brief Interrupt Handler Setter for COL4 pin input-sense-config functionality.
 *        Allows selecting an interrupt handler for COL4 at application runtime
 * @pre PIN_MANAGER_Initialize() has been called at least once
 * @param InterruptHandler function pointer.
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
/**
 * @ingroup  pinsdriver
 * @brief Default Interrupt Handler for COL5 pin. 
 *        This is a predefined interrupt handler to be used together with the COL5_SetInterruptHandler() method.
 *        This handler is called every time the COL5 ISR is executed. 
 * @pre PIN_MANAGER_Initialize() has been called at least once
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
/**
 * @ingroup  pinsdriver
 * @brief Interrupt Handler Setter for COL5 pin input-sense-config functionality.
 *        Allows selecting an interrupt handler for COL5 at application runtime
 * @pre PIN_MANAGER_Initialize() has been called at least once
 * @param InterruptHandler function pointer.
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
/**
 * @ingroup  pinsdriver
 * @brief Default Interrupt Handler for COL6 pin. 
 *        This is a predefined interrupt handler to be used together with the COL6_SetInterruptHandler() method.
 *        This handler is called every time the COL6 ISR is executed. 
 * @pre PIN_MANAGER_Initialize() has been called at least once
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
/**
 * @ingroup  pinsdriver
 * @brief Interrupt Handler Setter for COL6 pin input-sense-config functionality.
 *        Allows selecting an interrupt handler for COL6 at application runtime
 * @pre PIN_MANAGER_Initialize() has been called at least once
 * @param InterruptHandler function pointer.
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
/**
 * @ingroup  pinsdriver
 * @brief Default Interrupt Handler for COL7 pin. 
 *        This is a predefined interrupt handler to be used together with the COL7_SetInterruptHandler() method.
 *        This handler is called every time the COL7 ISR is executed. 
 * @pre PIN_MANAGER_Initialize() has been called at least once
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
/**
 * @ingroup  pinsdriver
 * @brief Interrupt Handler Setter for COL7 pin input-sense-config functionality.
 *        Allows selecting an interrupt handler for COL7 at application runtime
 * @pre PIN_MANAGER_Initialize() has been called at least once
 * @param InterruptHandler function pointer.
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
/**
 * @ingroup  pinsdriver
 * @brief Default Interrupt Handler for COL8 pin. 
 *        This is a predefined interrupt handler to be used together with the COL8_SetInterruptHandler() method.
 *        This handler is called every time the COL8 ISR is executed. 
 * @pre PIN_MANAGER_Initialize() has been called at least once
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
/**
 * @ingroup  pinsdriver
 * @brief Interrupt Handler Setter for COL8 pin input-sense-config functionality.
 *        Allows selecting an interrupt handler for COL8 at application runtime
 * @pre PIN_MANAGER_Initialize() has been called at least once
 * @param InterruptHandler function pointer.
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
/**
 * @ingroup  pinsdriver
 * @brief Default Interrupt Handler for COL9 pin. 
 *        This is a predefined interrupt handler to be used together with the COL9_SetInterruptHandler() method.
 *        This handler is called every time the COL9 ISR is executed. 
 * @pre PIN_MANAGER_Initialize() has been called at least once
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
/**
 * @ingroup  pinsdriver
 * @brief Interrupt Handler Setter for COL9 pin input-sense-config functionality.
 *        Allows selecting an interrupt handler for COL9 at application runtime
 * @pre PIN_MANAGER_Initialize() has been called at least once
 * @param InterruptHandler function pointer.
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
/**
 * @ingroup  pinsdriver
 * @brief Default Interrupt Handler for COL10 pin. 
 *        This is a predefined interrupt handler to be used together with the COL10_SetInterruptHandler() method.
 *        This handler is called every time the COL10 ISR is executed. 
 * @pre PIN_MANAGER_Initialize() has been called at least once
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
/**
 * @ingroup  pinsdriver
 * @brief Interrupt Handler Setter for COL10 pin input-sense-config functionality.
 *        Allows selecting an interrupt handler for COL10 at application runtime
 * @pre PIN_MANAGER_Initialize() has been called at least once
 * @param InterruptHandler function pointer.
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
/**
 * @ingroup  pinsdriver
 * @brief Default Interrupt Handler for COL11 pin. 
 *        This is a predefined interrupt handler to be used together with the COL11_SetInterruptHandler() method.
 *        This handler is called every time the COL11 ISR is executed. 
 * @pre PIN_MANAGER_Initialize() has been called at least once
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
/**
 * @ingroup  pinsdriver
 * @brief Interrupt Handler Setter for COL11 pin input-sense-config functionality.
 *        Allows selecting an interrupt handler for COL11 at application runtime
 * @pre PIN_MANAGER_Initialize() has been called at least once
 * @param InterruptHandler function pointer.
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
/**
 * @ingroup  pinsdriver
 * @brief Default Interrupt Handler for COL12 pin. 
 *        This is a predefined interrupt handler to be used together with the COL12_SetInterruptHandler() method.
 *        This handler is called every time the COL12 ISR is executed. 
 * @pre PIN_MANAGER_Initialize() has been called at least once
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
/**
 * @ingroup  pinsdriver
 * @brief Interrupt Handler Setter for COL12 pin input-sense-config functionality.
 *        Allows selecting an interrupt handler for COL12 at application runtime
 * @pre PIN_MANAGER_Initialize() has been called at least once
 * @param InterruptHandler function pointer.
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
/**
 * @ingroup  pinsdriver
 * @brief Default Interrupt Handler for COL14 pin. 
 *        This is a predefined interrupt handler to be used together with the COL14_SetInterruptHandler() method.
 *        This handler is called every time the COL14 ISR is executed. 
 * @pre PIN_MANAGER_Initialize() has been called at least once
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
/**
 * @ingroup  pinsdriver
 * @brief Interrupt Handler Setter for COL14 pin input-sense-config functionality.
 *        Allows selecting an interrupt handler for COL14 at application runtime
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
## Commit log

2024-08-25 Added progress plan
2024-08-29 added gitignore
2024-09-02 cv updates
2024-09-04 cv footer
2024-09-09 found leds and diodes
2024-11-07 keyboard code
2024-11-11 switched rows and colums, one row working now
2024-11-11 working! modifiers not implemented
2024-11-11 added some norwegian redefines
2024-11-26 added modifiers, missing alt gr
2024-11-26 second layer and windows button
2024-11-26 big refactor
2024-11-27 removed cv, added pictures
2024-11-27 new folder
2024-11-27 renaming
2024-11-27 readme update and renaming
2024-11-27 readme update
2024-11-29 added led project
2024-12-01 added pictures, gitignore, readme ish done
2025-01-16 deleting ignored files
2025-01-24 added 3d files for case
2025-01-27 build file mplab
2025-01-27 3d stl files
2025-01-28 Main picture update with pink case
2025-01-28 3d case text and images added
2025-01-28 title update
2025-01-28 * were not dots
2025-01-29 Generic led files
2025-01-29 new vid and pid
2025-01-29 usart0 periphal for leds
2025-01-29 config i think

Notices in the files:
full_keyboard_avrdu.X/mcc_generated_files/system/pins.h:
© [2025] Microchip Technology Inc. and its subsidiaries.
kicad_extra/footprints_extra/AVR64DU32_Curiosity_Nano.kicad_pcb:
Microchip © 2023
